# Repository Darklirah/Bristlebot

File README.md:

# One-of-a-Kind Mars Rover

> Dieses Projekt wurde mit Unterstützung von [Claude Code](https://claude.com/claude-code) entwickelt.

Linienfolgender, programmierbarer Zahnbürsten-Roboter auf ESP32, aufgebaut
auf einer eigenen Platine. Jedes Exemplar bekommt einen eigenen Namen und
ein eigenes WLAN (`MarsRover_Petra`), damit mehrere nebeneinander fahren
können.

> **Verwandt mit dem Bristlebot.** Der Mars Rover fährt nach demselben
> Prinzip wie ein *Bristlebot* — jener kleine Vibrationsläufer aus einem
> Zahnbürstenkopf, einem Unwuchtmotor und einer Knopfzelle, der über den
> Tisch summt. Er kann nur deutlich mehr: **zwei** Antriebe statt einem,
> damit er überhaupt lenken kann, zwei Augen für die Linie unter sich,
> Steuerung vom Handy und selbst geschriebene Fahrprogramme. Ein Bristlebot
> fährt, wohin er will — dieser hier fährt, wohin du willst.

*Die eigene Platine, 70 × 52 mm, zweilagig. Das ESP32-DevKit steckt quer auf
Buchsenleisten; links und rechts stehen Laderegler und Step-Up-Wandler
senkrecht als „Finnen". Weitere Ansichten mit Erklärung in
[Doku/04 §7](Doku/04_PCB-Layout-Empfehlung.md#7--so-ist-sie-geworden).*

**[→ Firmware direkt im Browser installieren](https://darklirah.github.io/One-of-a-Kind-Mars-Rover/)**

Die ausführliche Projektbeschreibung samt Programmier-Kapitel steht in
[Doku/00_Projektbeschreibung.md](Doku/00_Projektbeschreibung.md).

Zwei Vibrationsmotoren treiben zwei getrennte Borstenfelder an;
differentielle Vibrationsintensität lenkt. Zwei Reflexkoppler lesen die Linie,
ein PD-Regler hält ihn darauf. Gesteuert wird er über einen WLAN-Access-Point,
den der ESP32 selbst aufspannt — die Bedienoberfläche liefert er gleich mit.

**Status:** Hardware entworfen und geprüft, Firmware vollständig und
**fehlerfrei kompiliert** (0 Fehler, 0 Warnungen mit `-Wall`;
RAM 15,2 %, Flash 69,8 %) — **aber noch nie auf echter Hardware gelaufen.**

---

## Eckdaten

| | |
|---|---|
| Rechenkern | ESP32 DevKit V1, 30-Pin, gesteckt |
| Antrieb | 2× Vibrationsmotor 3 V über AO3400A Logik-MOSFET, 20 kHz PWM (LEDC) |
| Sensorik | 2× TCRT5000 analog an ADC1 (GPIO 34/35) |
| Lage | MPU-6050 am I²C: Drehen nach Winkel, Kurs halten, Kippschutz |
| Abstand | VL53L0X auf einem Mast: Hindernisse erkennen und umfahren |
| Anzeige | 4 LEDs: gelb vorne = Lenkrichtung, rot hinten = Status |
| Energie | LiPo 500 mAh, TP4056 über USB-C, MT3608 auf 5 V |
| Laufzeit | ≈ 1,2 h fahrend, ≈ 2,0 h Standby |
| Betriebsarten | Linie folgen · selbst fahren · Fahrprogramm |
| Fahrprogramme | 4 Speicherplätze im Flash, je 48 Schritte, Baukasten-Editor |
| Fernsteuerung | WLAN-AP + eigene Web-App, läuft auf iPhone **und** Android im Browser |
| Materialkosten | ≈ 26,50 € im Einzelstück |
| Masse | ≈ 40 g (größtes technisches Risiko, siehe Doku) |

## Bedienung in drei Schritten

1. Einschalten
2. Am Handy ins WLAN **`MarsRover_…`**, Passwort **`marsrover`**
3. Die Seite klappt von selbst auf — falls nicht: **`http://192.168.4.1`**

Nach dem Einschalten ist der Roboter **gesperrt**. Erst *Freigeben* in der App
lässt die Motoren laufen.

---

## Dokumentation

| Datei | Inhalt |
|---|---|
| [00 Projektbeschreibung](Doku/00_Projektbeschreibung.md) | Was das Projekt ist, alle Funktionen, ausführliches Kapitel zum Programmieren |
| [01 Schaltplan-Review](Doku/01_Schaltplan-Review.md) | Prüfung des Entwurfs: 5 Blocker, 9 Verbesserungen, Änderungsliste |
| [02 SMD vs. THT](Doku/02_SMD-vs-THT-Wirtschaftlichkeit.md) | Kostenvergleich bei 1/10/100 Stück, Massebudget, Laufzeitrechnung |
| [03 Stückliste](Doku/03_Stueckliste-BOM.md) | Vollständige BOM mit Bauteilkürzeln, Preisen und Einkaufsfallen |
| [04 PCB-Layout](Doku/04_PCB-Layout-Empfehlung.md) | Fertigungsparameter, Masseführung, Platzierung, Mechanik |
| [05 Pinbelegung](Doku/05_Pinbelegung.md) | Pinplan mit Begründungen, freie Pins, Vorzeichenkonventionen |
| [06 Fernsteuerung](Doku/06_Fernsteuerung-App.md) | Warum WLAN und nicht Bluetooth, Protokoll, fertige Apps als Rückfallebene |
| [07 Inbetriebnahme](Doku/07_Inbetriebnahme-und-Tuning.md) | Schrittweiser Aufbau, Kalibrierung, Reglerabstimmung, Fehlersuche |
| [Netzliste](Hardware/Netzliste.md) | Verbindungsliste als Vorlage für KiCad |
| [Projekt-Log](00_Projekt-Log.md) | Entscheidungen und offene Punkte |

## Firmware

```
Firmware/
  platformio.ini
  MarsRover/
    MarsRover.ino       Zustandsmaschine, PD-Regler, Telemetrie
    Config.h            Pins, Kennwerte, Feature-Flags  <- hier tunen
    RobotState.h        Betriebsart, Phase, Tuningstruktur
    Motors.*            PWM, Kennlinienspreizung, Kickstart, Duty-Begrenzung
    LineSensor.*        Median-Filter, Kalibrierung in NVS
    Leds.*              Blinkmuster
    RemoteControl.*     Access Point, Webserver, WebSocket, Protokoll
    WebUI.h             Bedienoberfläche, komplett inline
```

**Einzige externe Abhängigkeit:** `WebSockets` von Markus Sattler
(„arduinoWebSockets") ≥ 2.4.1. Läuft mit ESP32-Arduino-Core 2.x und 3.x — die
umgestellte LEDC-API wird per `#if` abgefangen.

Board: *ESP32 Dev Module*, 4 MB Flash, Partition *Default 4MB with spiffs*.

---

## Die wichtigsten vier Warnungen

1. **MT3608 vor dem ersten Anschluss des ESP32 im Leerlauf auf 5,00 V trimmen.**
   Die Module kommen mit beliebiger Einstellung, oft über 20 V. Das tötet das
   DevKit sofort.
2. **R_prog am TP4056 tauschen** — Werkszustand 1 A ist für eine 500-mAh-Zelle
   mehr als das Doppelte des Zulässigen. 4,7 kΩ ergibt 255 mA.
3. **USB-C braucht 2× 5,1 kΩ an CC1 und CC2 nach GND**, sonst liefert ein
   USB-C-Netzteil keine Spannung.
4. **Zwei getrennte Borstenfelder, eines unter jedem Motor.** Auf einer
   gemeinsamen Grundplatte mittelt sich die Vibrationsdifferenz weg und der
   Roboter lenkt praktisch nicht.

## Lizenz

[GNU General Public License v3.0](LICENSE)

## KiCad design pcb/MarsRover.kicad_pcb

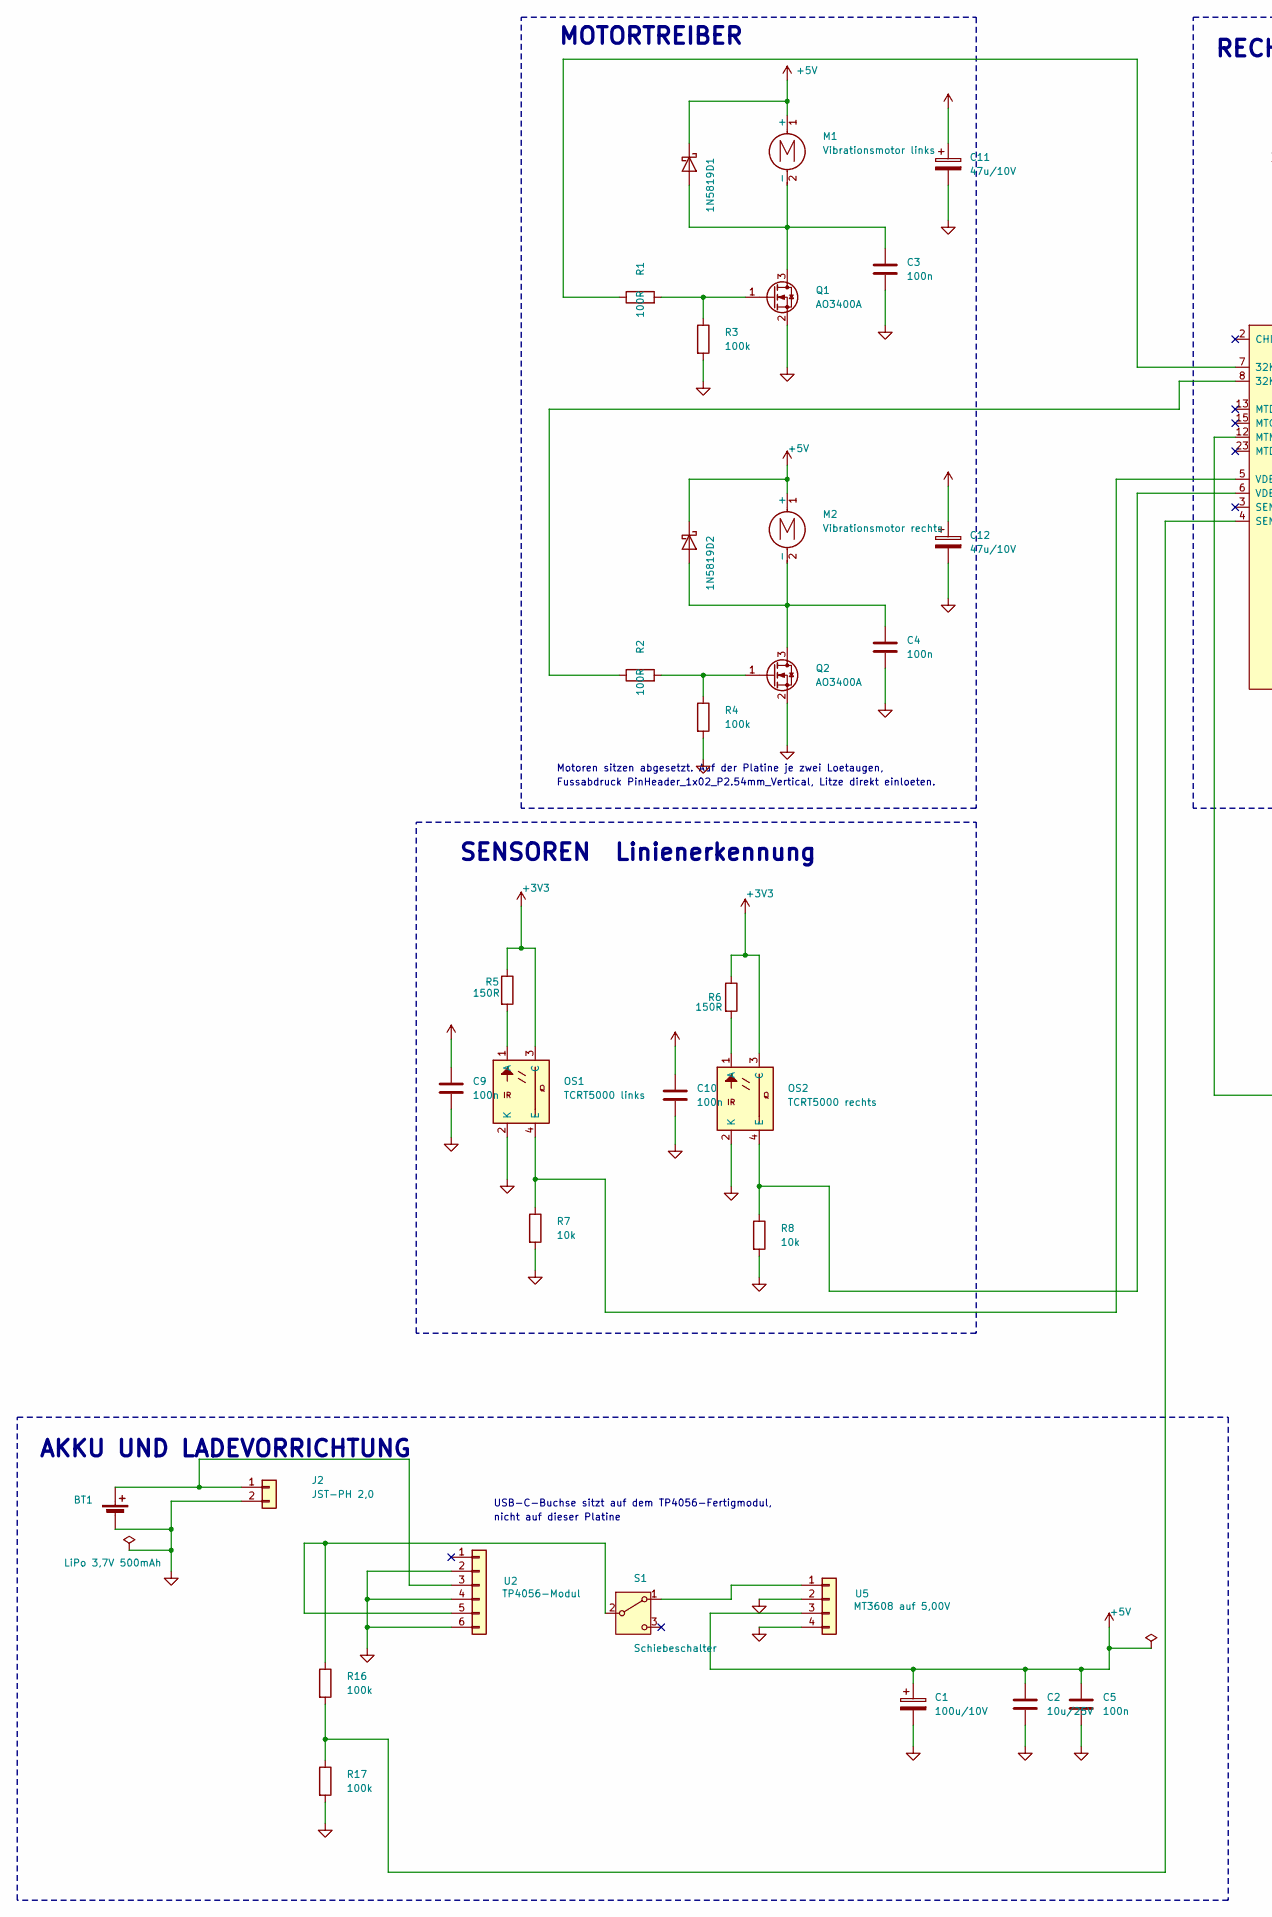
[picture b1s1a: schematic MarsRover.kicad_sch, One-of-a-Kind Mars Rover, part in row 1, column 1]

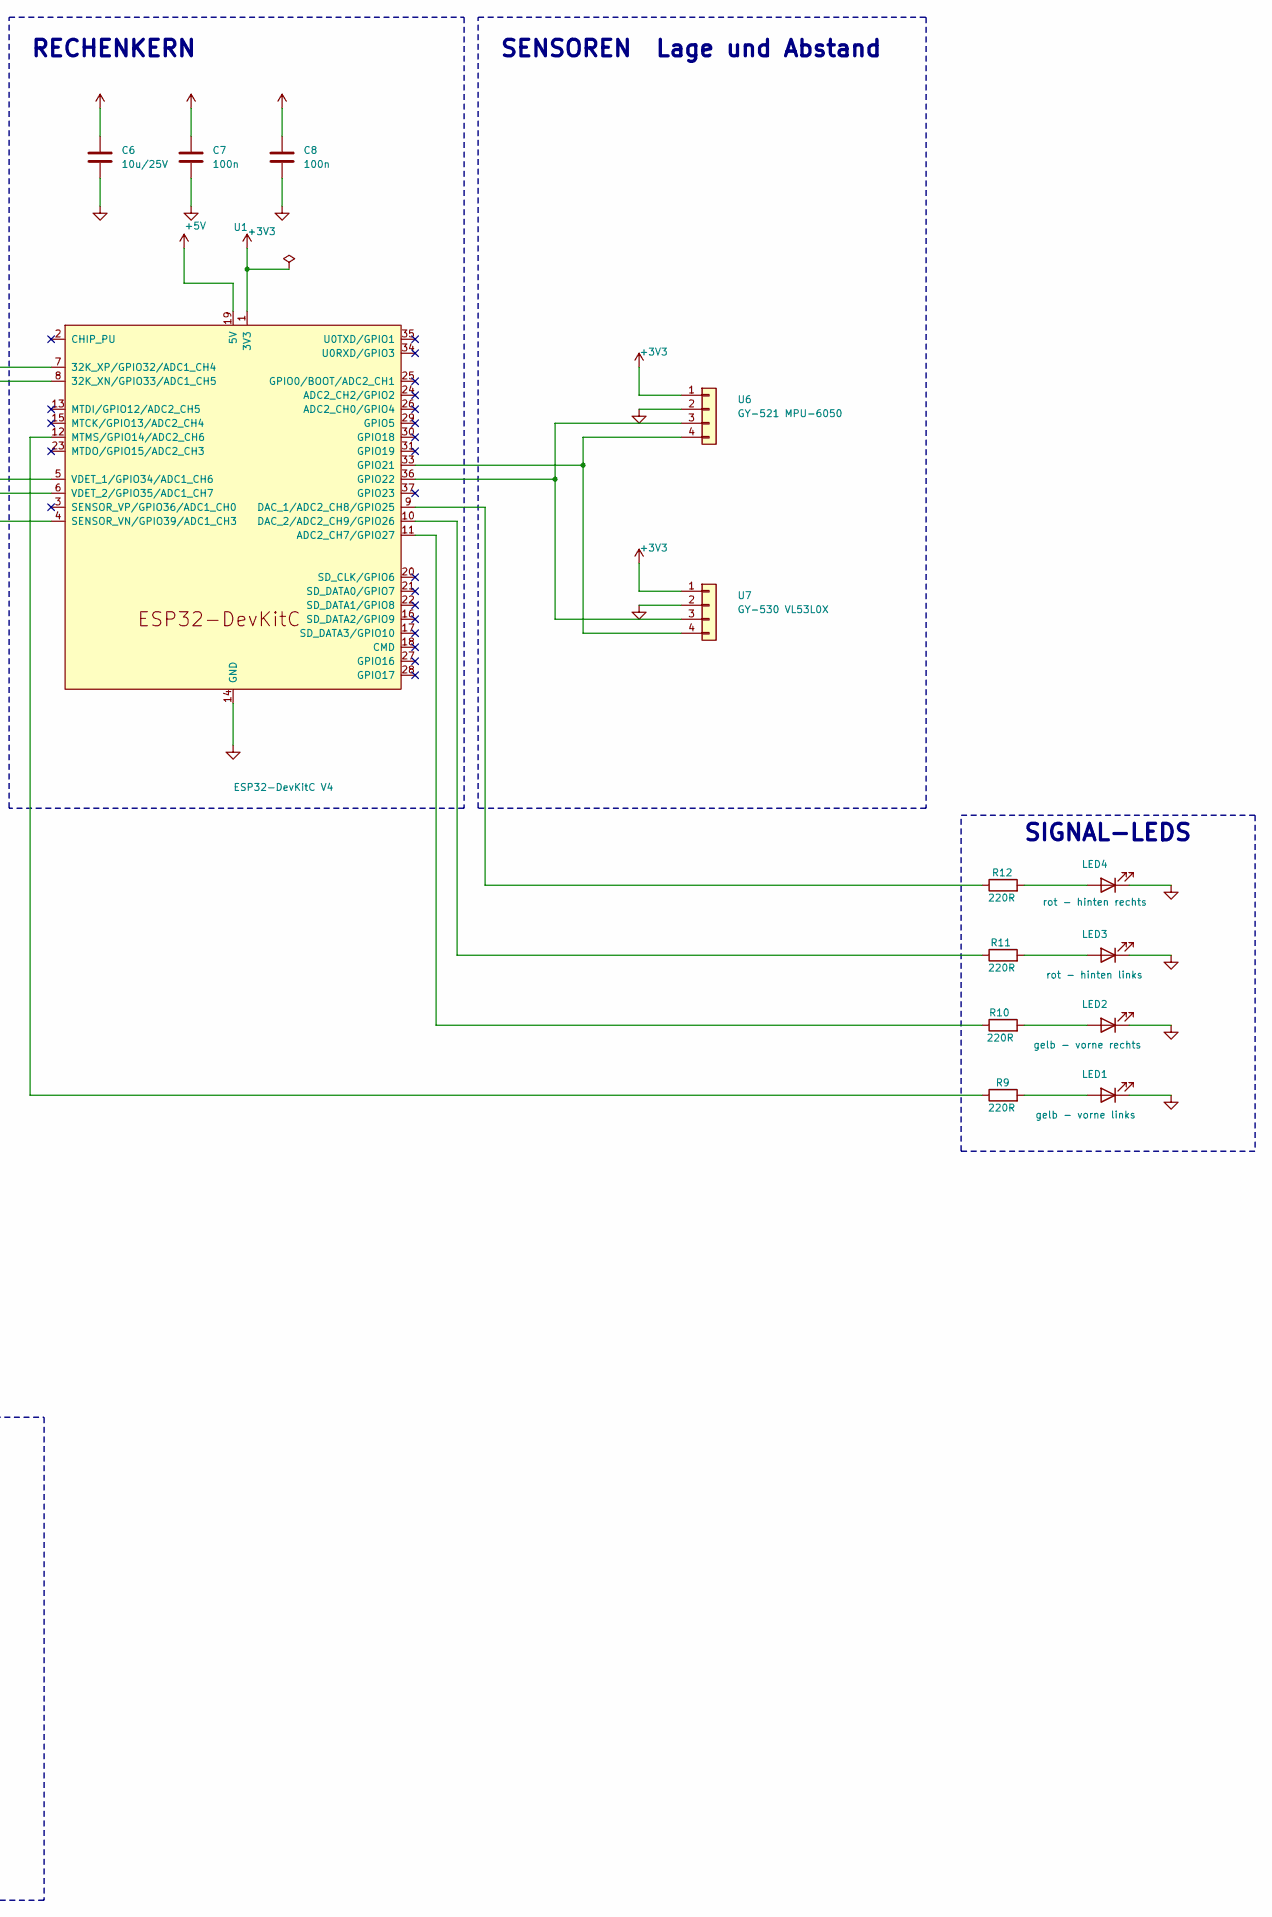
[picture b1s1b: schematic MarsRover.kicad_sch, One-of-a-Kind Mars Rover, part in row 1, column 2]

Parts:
BT1: LiPo 3,7V 500mAh
C1: 100u/10V; CP_Radial_D6.3mm_P2.50mm
C2, C6: 10u/25V; C_0805_2012Metric
C3, C4, C5, C7, C8, C9, C10: 100n; C_0805_2012Metric
C11, C12: 47u/10V; CP_Radial_D5.0mm_P2.00mm
D1, D2: 1N5819; D_DO-41_SOD81_P7.62mm_Horizontal
J2: JST-PH 2,0; JST_PH_S2B-PH-K_1x02_P2.00mm_Horizontal
LED1: gelb - vorne links; LED_D3.0mm
LED2: gelb - vorne rechts; LED_D3.0mm
LED3: rot - hinten links; LED_D3.0mm
LED4: rot - hinten rechts; LED_D3.0mm
M1: Vibrationsmotor links; PinHeader_1x02_P2.54mm_Vertical
M2: Vibrationsmotor rechts; PinHeader_1x02_P2.54mm_Vertical
OS1: TCRT5000 links; Vishay_TCRT5000
OS2: TCRT5000 rechts; Vishay_TCRT5000
Q1, Q2: AO3400A; SOT-23
R1, R2: 100R; R_0805_2012Metric_Pad1.20x1.40mm_HandSolder
R3, R4, R16, R17: 100k; R_0805_2012Metric_Pad1.20x1.40mm_HandSolder
R5, R6: 150R; R_0805_2012Metric_Pad1.20x1.40mm_HandSolder
R7, R8: 10k; R_0805_2012Metric_Pad1.20x1.40mm_HandSolder
R9, R10, R11, R12: 220R; R_Axial_DIN0207_L6.3mm_D2.5mm_P7.62mm_Horizontal
S1: Schiebeschalter; SW_Slide_SPDT_Straight_CK_OS102011MS2Q
U1: ESP32-DevKitC V4; ESP32-DevKitC
U2: TP4056-Modul; PinHeader_1x06_P2.54mm_Vertical
U5: MT3608 auf 5,00V; PinHeader_1x04_P2.54mm_Vertical
U6: GY-521 MPU-6050; PinHeader_1x04_P2.54mm_Vertical
U7: GY-530 VL53L0X; PinHeader_1x04_P2.54mm_Vertical

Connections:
+3V3: C8.1, C9.1, C10.1, OS1.3 (C), OS2.3 (C), R5.1, R6.1, U1.1 (3V3), U6.1, U7.1
+5V: C1.1, C2.1, C5.1, C6.1, C7.1, C11.1, C12.1, D1.1 (K), D2.1 (K), M1.1 (+), M2.1 (+), U1.19 (5V), U5.3
GND: BT1.2 (-), C1.2, C2.2, C3.2, C4.2, C5.2, C6.2, C7.2, C8.2, C9.2, C10.2, C11.2, C12.2, J2.2, LED1.1 (K), LED2.1 (K), LED3.1 (K), LED4.1 (K), OS1.2 (K), OS2.2 (K), Q1.2 (S), Q2.2 (S), R3.2, R4.2, R7.2, R8.2, R17.2, U1.14 (GND), U1.32 (GND), U1.38 (GND), U2.2, U2.4, U2.6, U5.2, U5.4, U6.2, U7.2
unnamed: C3.1, D1.2 (A), M1.2 (-), Q1.3 (D)
unnamed: C4.1, D2.2 (A), M2.2 (-), Q2.3 (D)
unnamed: BT1.1 (+), J2.1, U2.3
unnamed: LED1.2 (A), R9.2
unnamed: LED2.2 (A), R10.2
unnamed: LED3.2 (A), R11.2
unnamed: LED4.2 (A), R12.2
unnamed: OS1.1 (A), R5.2
unnamed: OS1.4 (E), R7.1, U1.5 (VDET_1/GPIO34/ADC1_CH6)
unnamed: OS2.1 (A), R6.2
unnamed: OS2.4 (E), R8.1, U1.6 (VDET_2/GPIO35/ADC1_CH7)
unnamed: Q1.1 (G), R1.2, R3.1
unnamed: Q2.1 (G), R2.2, R4.1
unnamed: S1.1 (A), U5.1
unnamed: R16.1, S1.2 (B), U2.5
unnamed: R2.1, U1.8 (32K_XN/GPIO33/ADC1_CH5)
unnamed: R1.1, U1.7 (32K_XP/GPIO32/ADC1_CH4)
unnamed: R10.1, U1.11 (ADC2_CH7/GPIO27)
unnamed: R12.1, U1.9 (DAC_1/ADC2_CH8/GPIO25)
unnamed: R11.1, U1.10 (DAC_2/ADC2_CH9/GPIO26)
unnamed: U1.33 (GPIO21), U6.4, U7.4
unnamed: U1.36 (GPIO22), U6.3, U7.3
unnamed: R9.1, U1.12 (MTMS/GPIO14/ADC2_CH6)
unnamed: R16.2, R17.1, U1.4 (SENSOR_VN/GPIO39/ADC1_CH3)

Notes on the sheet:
Motoren sitzen abgesetzt. Auf der Platine je zwei Loetaugen,
MOTORTREIBER
SENSOREN Linienerkennung
USB-C-Buchse sitzt auf dem TP4056-Fertigmodul,
SIGNAL-LEDS
Fussabdruck PinHeader_1x02_P2.54mm_Vertical, Litze direkt einloeten.
AKKU UND LADEVORRICHTUNG
RECHENKERN
nicht auf dieser Platine
SENSOREN Lage und Abstand

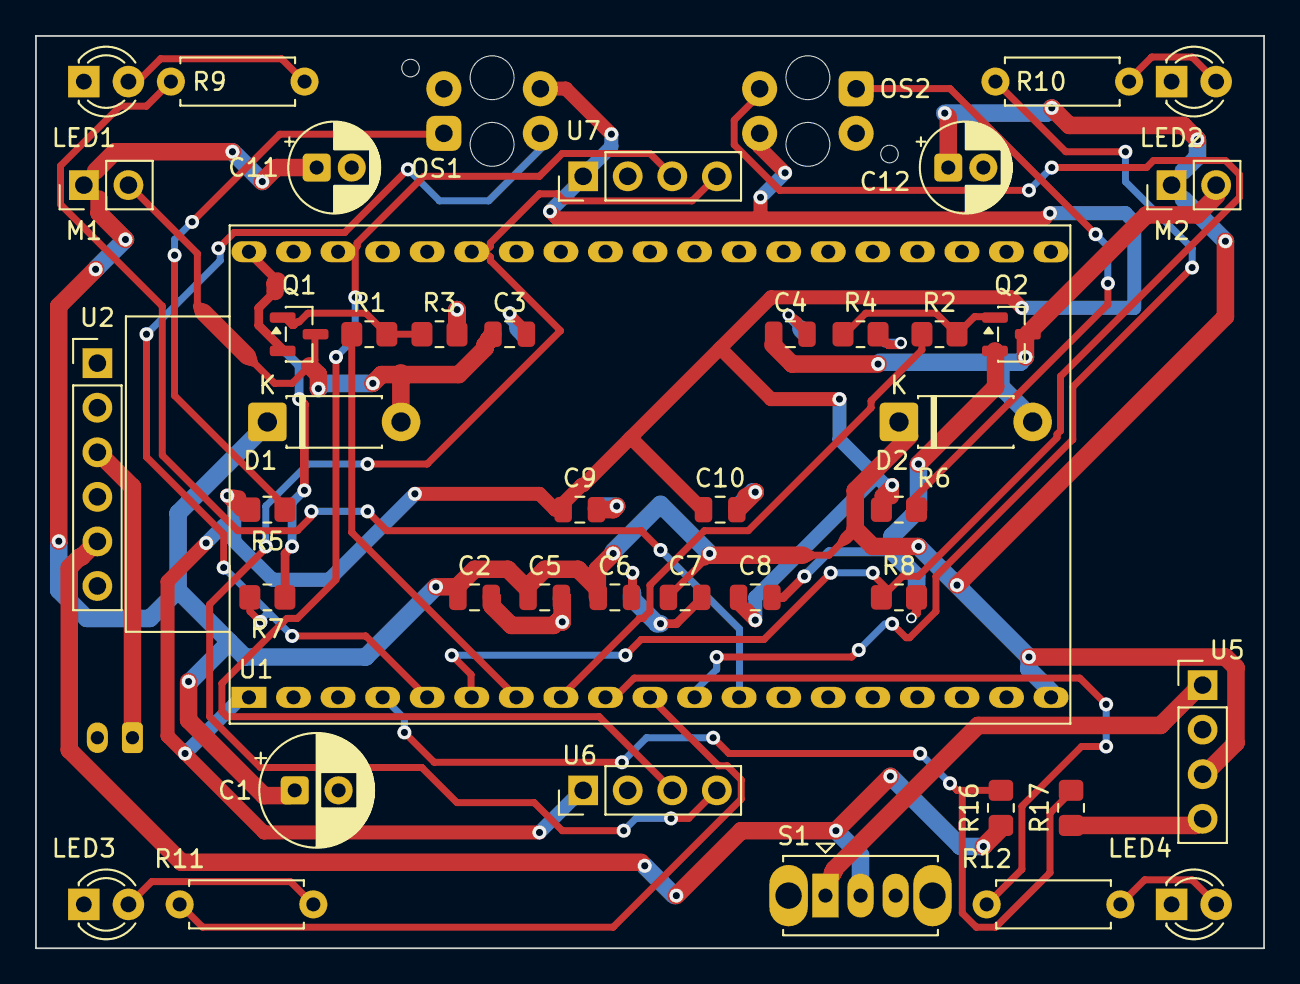
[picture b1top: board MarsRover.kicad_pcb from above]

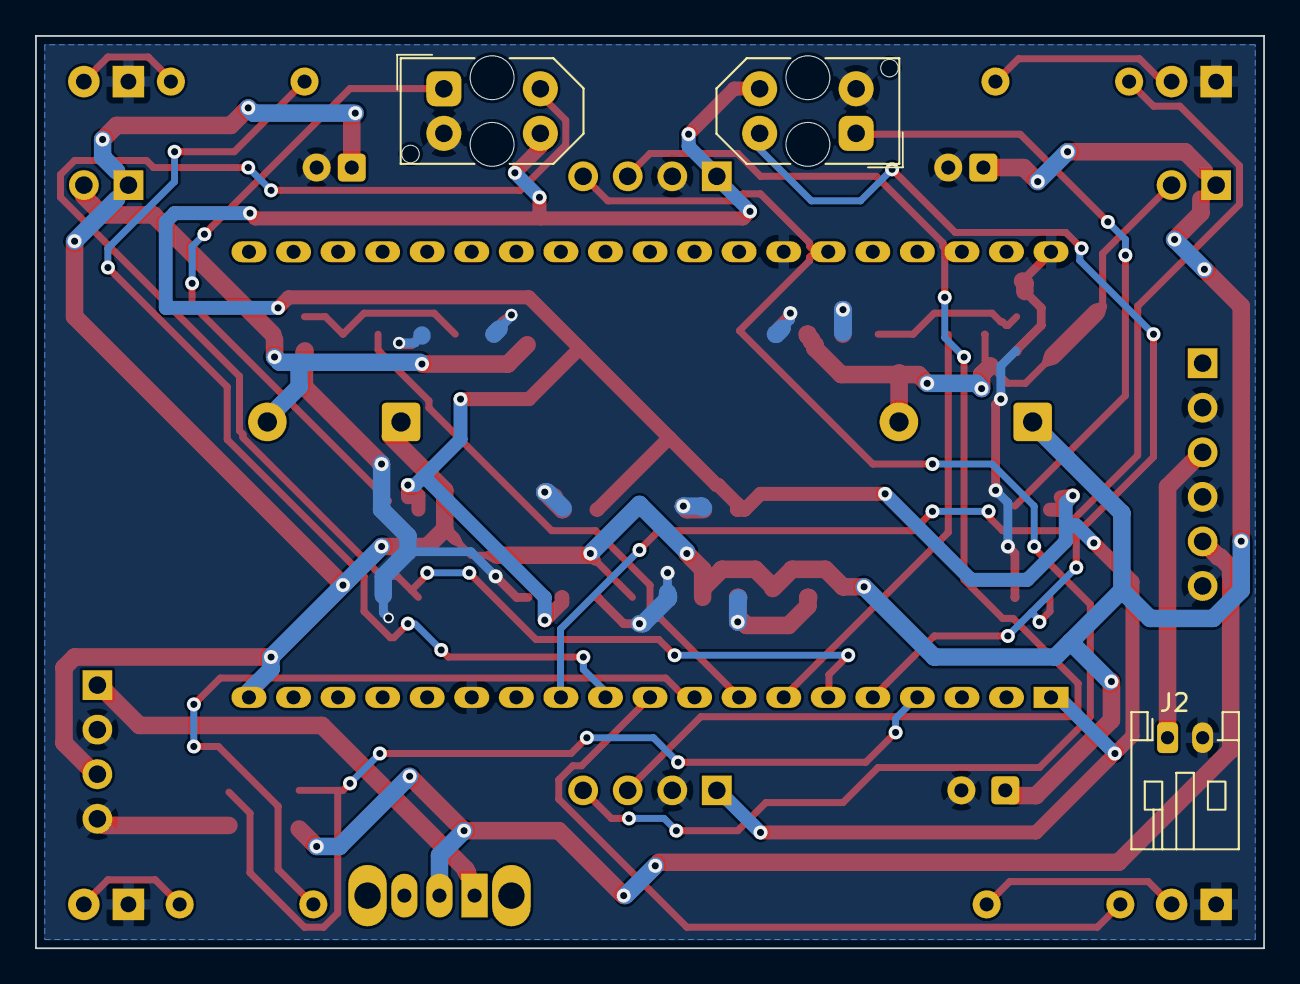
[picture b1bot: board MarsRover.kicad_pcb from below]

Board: 2 copper layers, 70.0 x 52.0 mm, 45 parts (3 on the bottom side), 27 nets.

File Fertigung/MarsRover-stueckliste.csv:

"Referenzen","Wert","Fussabdruck","Menge","Hinweis"
"BT1","LiPo 3,7V 500mAh","","1",""
"C1","100u/10V","Capacitor_THT:CP_Radial_D6.3mm_P2.50mm","1",""
"C2,C6","10u/25V","Capacitor_SMD:C_0805_2012Metric","2",""
"C3-C5,C7-C10","100n","Capacitor_SMD:C_0805_2012Metric","7",""
"C11,C12","47u/10V","Capacitor_THT:CP_Radial_D5.0mm_P2.00mm","2",""
"D1,D2","1N5819","Diode_THT:D_DO-41_SOD81_P7.62mm_Horizontal","2",""
"J2","JST-PH 2,0","Connector_JST:JST_PH_S2B-PH-K_1x02_P2.00mm_Horizontal","1",""
"LED1","gelb - vorne links","LED_THT:LED_D3.0mm","1",""
"LED2","gelb - vorne rechts","LED_THT:LED_D3.0mm","1",""
"LED3","rot - hinten links","LED_THT:LED_D3.0mm","1",""
"LED4","rot - hinten rechts","LED_THT:LED_D3.0mm","1",""
"M1","Vibrationsmotor links","Connector_PinHeader_2.54mm:PinHeader_1x02_P2.54mm_Vertical","1","Motor sitzt abgesetzt, Anschluss ueber zwei Loetaugen"
"M2","Vibrationsmotor rechts","Connector_PinHeader_2.54mm:PinHeader_1x02_P2.54mm_Vertical","1","Motor sitzt abgesetzt, Anschluss ueber zwei Loetaugen"
"OS1","TCRT5000 links","OptoDevice:Vishay_TCRT5000","1",""
"OS2","TCRT5000 rechts","OptoDevice:Vishay_TCRT5000","1",""
"Q1,Q2","AO3400A","Package_TO_SOT_SMD:SOT-23","2",""
"R1,R2","100R","Resistor_SMD:R_0805_2012Metric_Pad1.20x1.40mm_HandSolder","2",""
"R3,R4,R16,R17","100k","Resistor_SMD:R_0805_2012Metric_Pad1.20x1.40mm_HandSolder","4",""
"R5,R6","150R","Resistor_SMD:R_0805_2012Metric_Pad1.20x1.40mm_HandSolder","2",""
"R7,R8","10k","Resistor_SMD:R_0805_2012Metric_Pad1.20x1.40mm_HandSolder","2",""
"R9-R12","220R","Resistor_THT:R_Axial_DIN0207_L6.3mm_D2.5mm_P7.62mm_Horizontal","4",""
"S1","Schiebeschalter","Button_Switch_THT:SW_Slide_SPDT_Straight_CK_OS102011MS2Q","1",""
"U1","ESP32-DevKitC V4","PCM_Espressif:ESP32-DevKitC","1",""
"U2","TP4056-Modul","Connector_PinHeader_2.54mm:PinHeader_1x06_P2.54mm_Vertical","1",""
"U5","MT3608 auf 5,00V","Connector_PinHeader_2.54mm:PinHeader_1x04_P2.54mm_Vertical","1",""
"U6","GY-521 MPU-6050","Connector_PinHeader_2.54mm:PinHeader_1x04_P2.54mm_Vertical","1",""
"U7","GY-530 VL53L0X","Connector_PinHeader_2.54mm:PinHeader_1x04_P2.54mm_Vertical","1",""

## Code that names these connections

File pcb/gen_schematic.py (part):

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COMPONENTS = [
    ("U1", "Espressif", "ESP32-DevKitC", "ESP32-DevKitC V4", (30, 40), {
        "1":  "+3V3",
        "4":  "VBAT_SENSE",   # GPIO39, optional
        "5":  "LINE_L",       # GPIO34
        "6":  "LINE_R",       # GPIO35
        "7":  "MOT_L_G",      # GPIO32
        "8":  "MOT_R_G",      # GPIO33
        "9":  "LED_RR",       # GPIO25
        "10": "LED_RL",       # GPIO26
        "11": "LED_FR",       # GPIO27
        "12": "LED_FL",       # GPIO14
        "14": "GND",
        "19": "+5V",
        "32": "GND",
        "33": "I2C_SDA",      # GPIO21
        "36": "I2C_SCL",      # GPIO22
        "38": "GND",
    }),

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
